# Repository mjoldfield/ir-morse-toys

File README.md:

# Games with Morse Code at 940nm

This repository contains designs for two detectors and two transmitters
for Morse Code signals, all working with 940nm infra-red light.

You can read more on [my website](https://mjoldfield.com/atelier/2022/01/ir-fun.html).

If you’re near Cambridge, UK you might enjoy the [geocache](https://www.geocaching.com/geocache/GC86BQY_to-the-birdhouse)
 for which they were designed.

## Building the firmware

There are three steps:

  1. Install a GNU toolchain. You can download this from
	 [ARM](https://developer.arm.com/Tools%20and%20Software/GNU%20Toolchain),
	 but it is often available as system package in e.g. Debian.

  1. Install [libopencm3](https://libopencm3.org):

		$ git submodule init
		
		$ git submodule upgrade

		$ make -C libopencm3

  1. Compile the firmware

		$ make -C tx-bluepill/firmware

		$ make -C tx-stm32l431/firmware

The libopencm3-rules.mk file contains a number of fake targets to flash the firmware.

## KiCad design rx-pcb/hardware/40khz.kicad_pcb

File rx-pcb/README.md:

# A PCB based Detector

You can read more on [my website](https://mjoldfield.com/atelier/2022/01/rx-pcb.html).

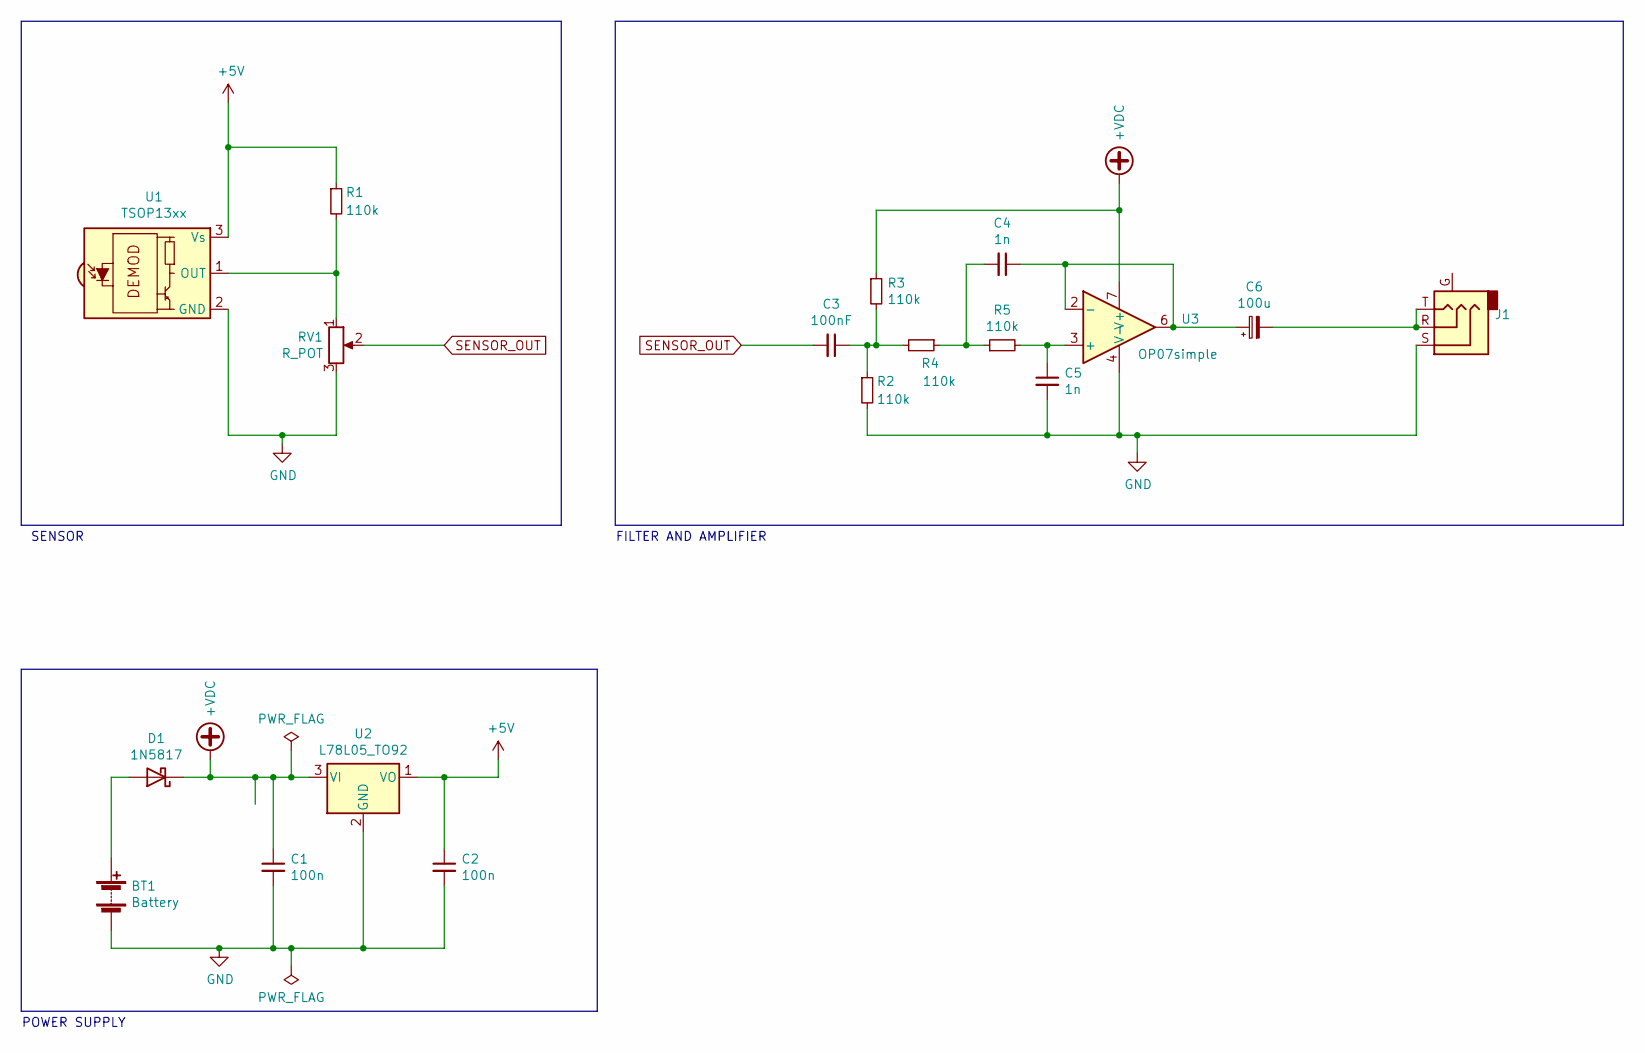
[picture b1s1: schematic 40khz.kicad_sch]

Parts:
BT1: Battery; Battery_Keystone_968
C1, C2: 100n; C_Disc_D10.0mm_W2.5mm_P5.00mm
C3: 100nF; C_Disc_D10.0mm_W2.5mm_P5.00mm
C4, C5: 1n; C_Rect_L10.0mm_W5.0mm_P5.00mm_P7.50mm
C6: 100u; CP_Radial_D6.3mm_P2.50mm
D1: 1N5817; D_DO-41_SOD81_P10.16mm_Horizontal
J1: AudioJack3_Ground; TruConnect_3.5mm_StereoSocket
R1, R2, R3, R4, R5: 110k; R_Axial_DIN0207_L6.3mm_D2.5mm_P10.16mm_Horizontal
RV1: R_POT; Potentiometer_Piher_PC-16_Single_Horizontal
U1: TSOP13xx; Vishay_MINIMOLD-3Pin
U2: L78L05_TO92; TO-92_Inline
U3: OP07simple; DIP-8_W7.62mm_Socket

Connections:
+5V: C2.1, R1.1, U1.3 (Vs), U2.1 (VO)
+VDC: C1.1, D1.1 (K), R3.1, U2.3 (VI), U3.7 (V+)
GND: BT1.2 (-), C1.2, C2.2, C5.2, J1.S, R2.2, RV1.3, U1.2 (GND), U2.2 (GND), U3.4 (V-)
unnamed: BT1.1 (+), D1.2 (A)
unnamed: C3.1, R2.1, R3.2, R4.2
unnamed: C4.1, C6.1, U3.2 (-), U3.6
unnamed: C4.2, R4.1, R5.1
unnamed: C5.1, R5.2, U3.3 (+)
unnamed: C6.2, J1.R, J1.T
unnamed: R1.2, RV1.1, U1.1 (OUT)
SENSOR_OUT: C3.2, RV1.2

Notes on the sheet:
SENSOR
POWER SUPPLY
FILTER AND AMPLIFIER

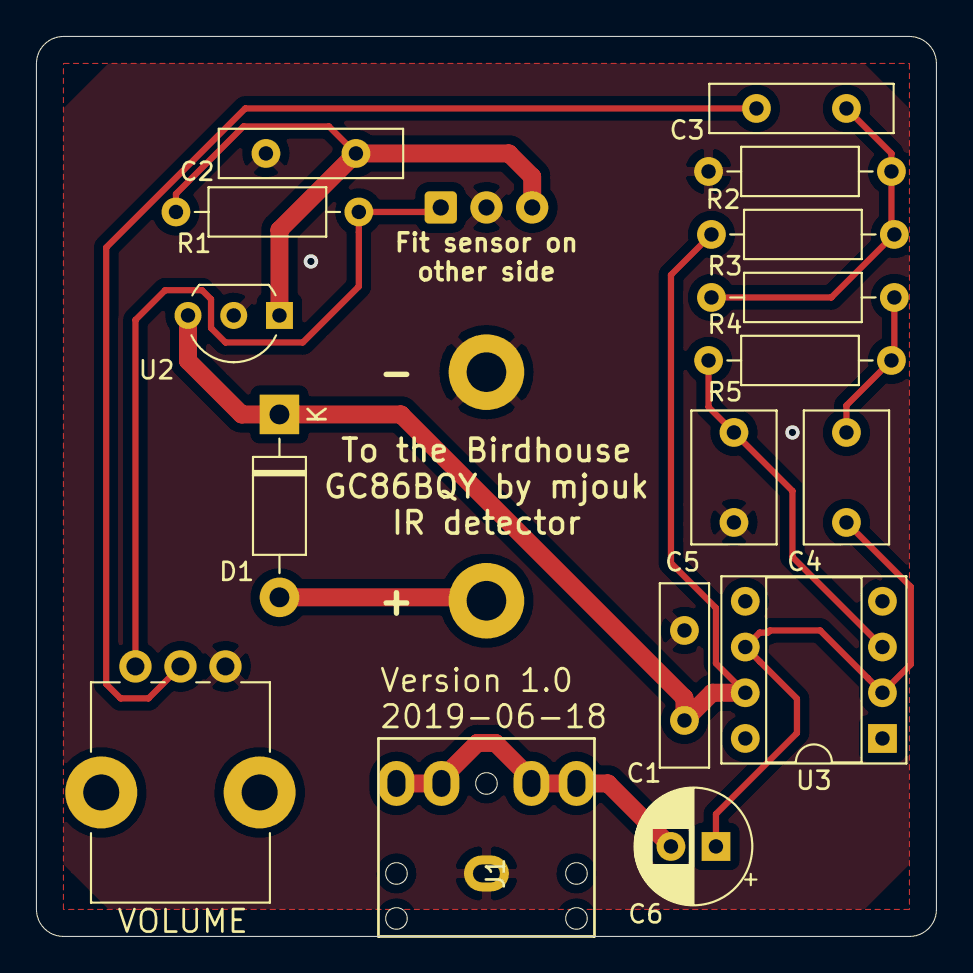
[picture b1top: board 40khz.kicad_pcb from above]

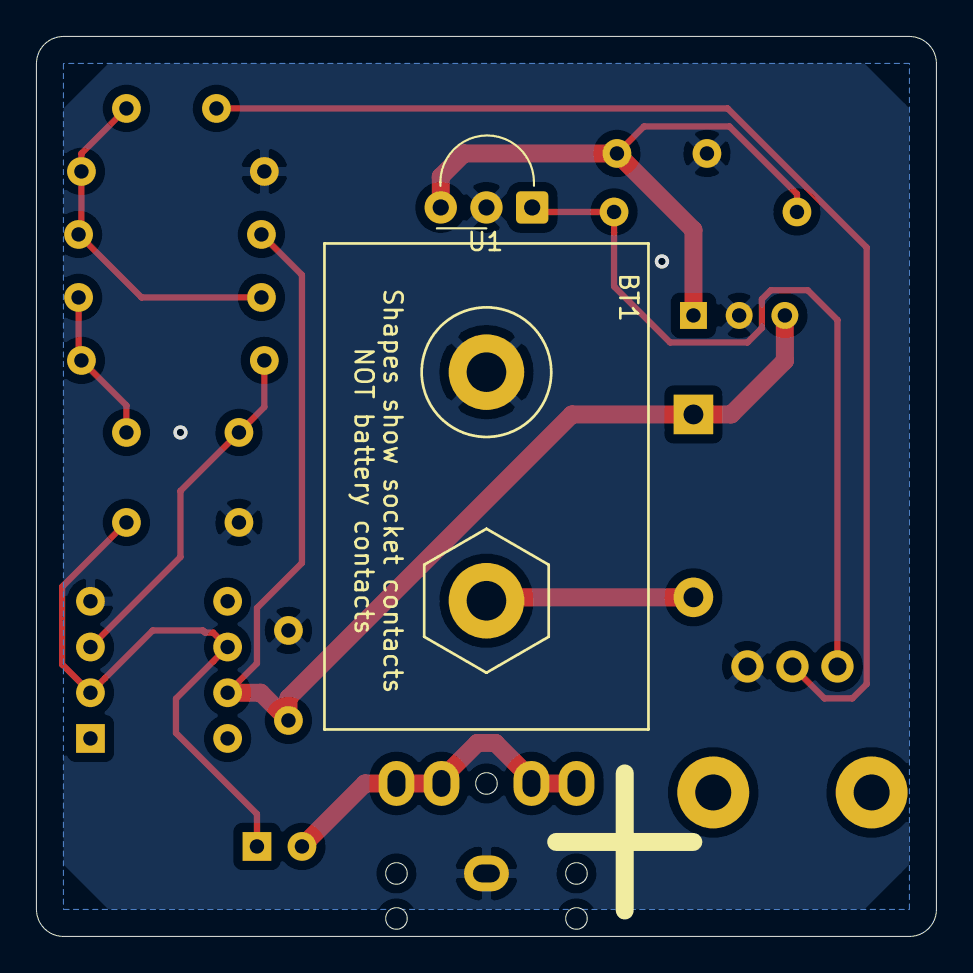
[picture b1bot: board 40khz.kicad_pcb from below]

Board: 2 copper layers, 50.0 x 50.0 mm, 18 parts (2 on the bottom side), 11 nets.

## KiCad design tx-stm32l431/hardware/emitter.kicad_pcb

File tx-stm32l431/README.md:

# A STM32L431 based emitter

You can read more on [my website](https://mjoldfield.com/atelier/2022/01/ir-emitter-bb.html).

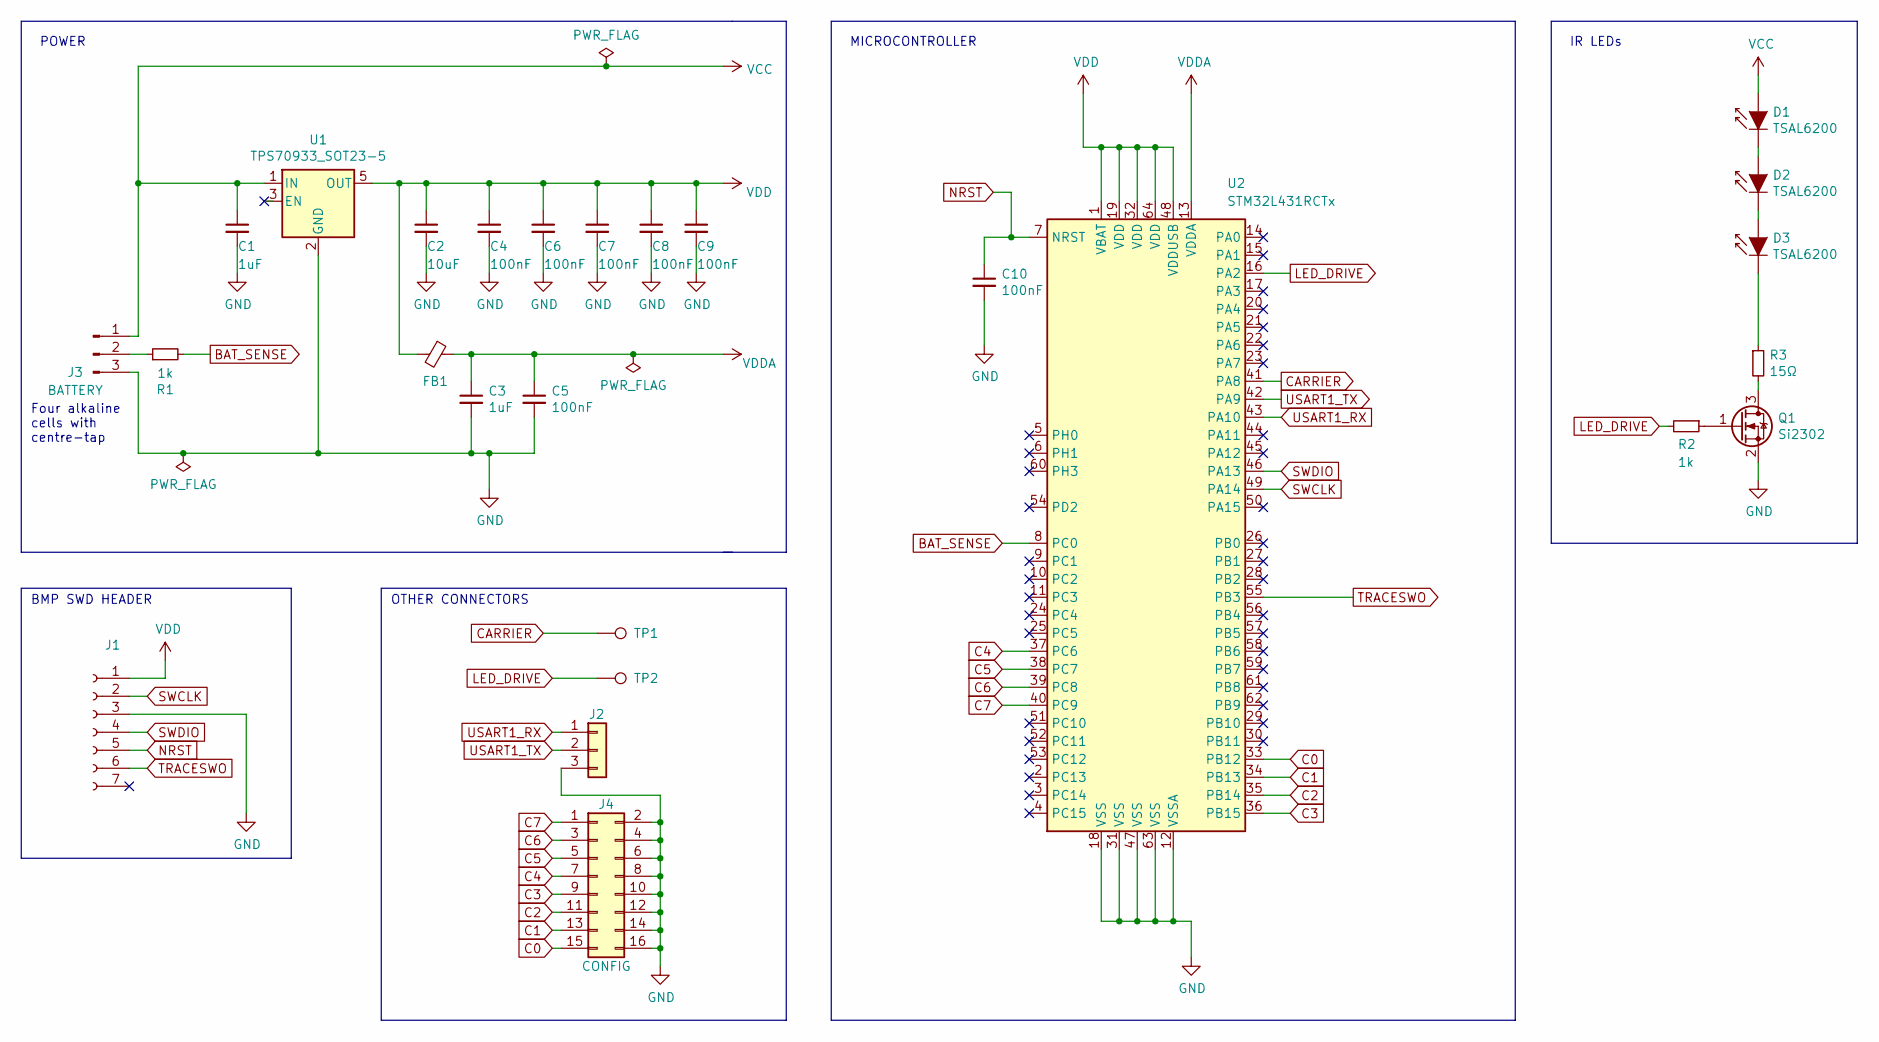
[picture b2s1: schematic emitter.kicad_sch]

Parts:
C1, C3: 1uF; C_0603_1608Metric_Pad1.05x0.95mm_HandSolder
C2: 10uF; C_0603_1608Metric_Pad1.05x0.95mm_HandSolder
C4, C5, C6, C7, C8, C9, C10: 100nF; C_0603_1608Metric_Pad1.05x0.95mm_HandSolder
D1, D2, D3: TSAL6200; LED_D5.0mm_Horizontal_O1.27mm_Z3.0mm_IRBlack
FB1: Ferrite_Bead_Small; L_0603_1608Metric_Pad1.05x0.95mm_HandSolder
J1: Conn_01x07_Female; PinSocket_1x07_P2.54mm_Vertical
J2: Conn_01x03; PinSocket_1x03_P2.54mm_Vertical
J3: BATTERY; PinHeader_1x03_P2.54mm_Vertical
J4: CONFIG; PinHeader_2x08_P2.54mm_Vertical
Q1: Si2302; SOT-23
R1, R2: 1k; R_0603_1608Metric_Pad1.05x0.95mm_HandSolder
R3: 15Ω; R_0603_1608Metric_Pad1.05x0.95mm_HandSolder
TP1, TP2: TestPoint; TestPoint_Loop_D2.60mm_Drill1.4mm_Beaded
U1: TPS70933_SOT23-5; SOT-23-5
U2: STM32L431RCTx; LQFP-64_10x10mm_P0.5mm

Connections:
BAT_SENSE: R1.2, U2.8 (PC0)
C0: J4.15, U2.33 (PB12)
C1: J4.13, U2.34 (PB13)
C2: J4.11, U2.35 (PB14)
C3: J4.9, U2.36 (PB15)
C4: J4.7, U2.37 (PC6)
C5: J4.5, U2.38 (PC7)
C6: J4.3, U2.39 (PC8)
C7: J4.1, U2.40 (PC9)
CARRIER: TP1.1, U2.41 (PA8)
GND: C1.2, C2.2, C3.2, C4.2, C5.2, C6.2, C7.2, C8.2, C9.2, C10.2, J1.3, J2.3, J3.3, J4.2, J4.4, J4.6, J4.8, J4.10, J4.12, J4.14, J4.16, Q1.2 (S), U1.2 (GND), U2.12 (VSSA), U2.18 (VSS), U2.31 (VSS), U2.47 (VSS), U2.63 (VSS)
LED_DRIVE: R2.2, TP2.1, U2.16 (PA2)
NRST: C10.1, J1.5, U2.7 (NRST)
unnamed: D1.1 (K), D2.2 (A)
unnamed: D2.1 (K), D3.2 (A)
unnamed: D3.1 (K), R3.1
unnamed: J3.2, R1.1
unnamed: Q1.1 (G), R2.1
unnamed: Q1.3 (D), R3.2
SWCLK: J1.2, U2.49 (PA14)
SWDIO: J1.4, U2.46 (PA13)
TRACESWO: J1.6, U2.55 (PB3)
USART1_RX: J2.1, U2.43 (PA10)
USART1_TX: J2.2, U2.42 (PA9)
VCC: C1.1, D1.2 (A), J3.1, U1.1 (IN)
VDD: C2.1, C4.1, C6.1, C7.1, C8.1, C9.1, FB1.2, J1.1, U1.5 (OUT), U2.1 (VBAT), U2.19 (VDD), U2.32 (VDD), U2.48 (VDDUSB), U2.64 (VDD)
VDDA: C3.1, C5.1, FB1.1, U2.13 (VDDA)

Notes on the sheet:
BMP SWD HEADER
IR LEDs
MICROCONTROLLER
OTHER CONNECTORS
POWER
Four alkaline cells with centre-tap

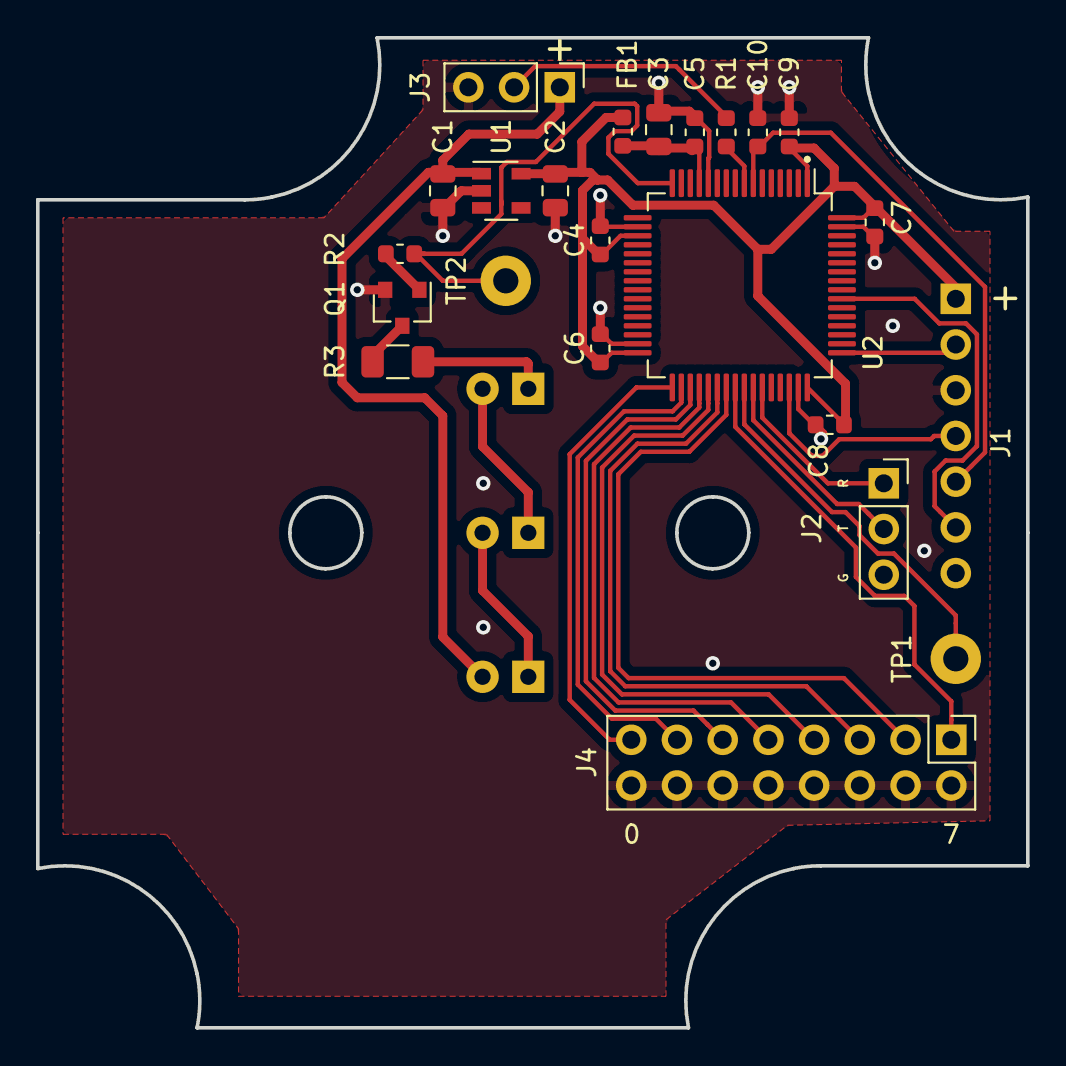
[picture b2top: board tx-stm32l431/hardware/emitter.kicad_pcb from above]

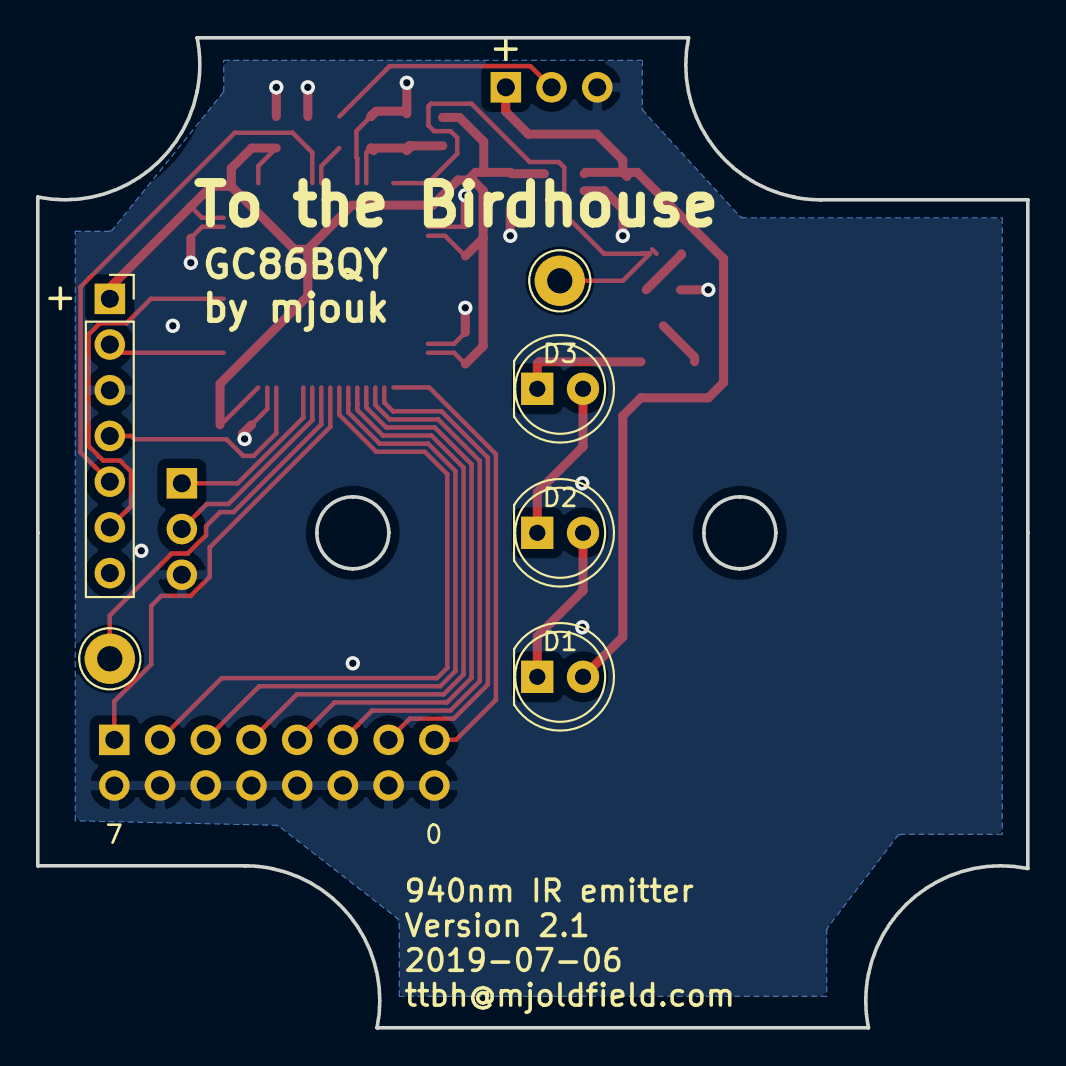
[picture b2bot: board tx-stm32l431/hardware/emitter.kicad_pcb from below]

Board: 2 copper layers, 55.0 x 55.0 mm, 26 parts (6 on the bottom side), 27 nets.

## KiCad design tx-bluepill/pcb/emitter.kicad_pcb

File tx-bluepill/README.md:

# A Bluepill STM32F103 based emitter

You can read more on [my website](https://mjoldfield.com/atelier/2022/01/ir-emitter-bp.html).

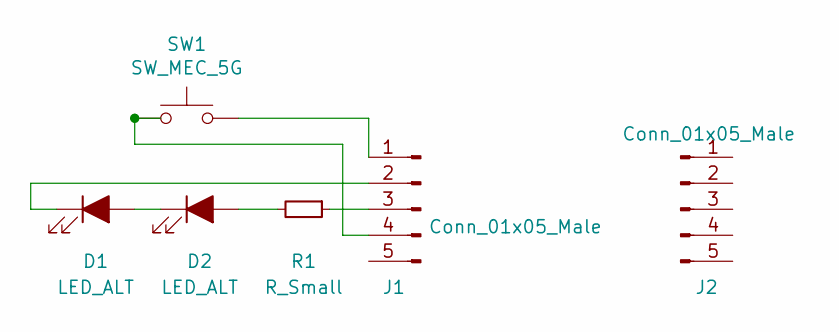
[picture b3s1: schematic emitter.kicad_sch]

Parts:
D1, D2: LED_ALT; LED_D5.0mm
J1, J2: Conn_01x05_Male; PinHeader_1x05_P2.54mm_Vertical
R1: R_Small; R_Axial_DIN0204_L3.6mm_D1.6mm_P5.08mm_Horizontal
SW1: SW_MEC_5G; SW_TH_Tactile_Omron_B3F-10xx

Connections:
unnamed: D1.1 (K), J1.2
unnamed: D1.2 (A), D2.1 (K)
unnamed: D2.2 (A), R1.2
unnamed: J1.1, SW1.3 (B), SW1.4 (B)
unnamed: J1.3, R1.1
unnamed: J1.4, SW1.1 (A), SW1.2 (A)

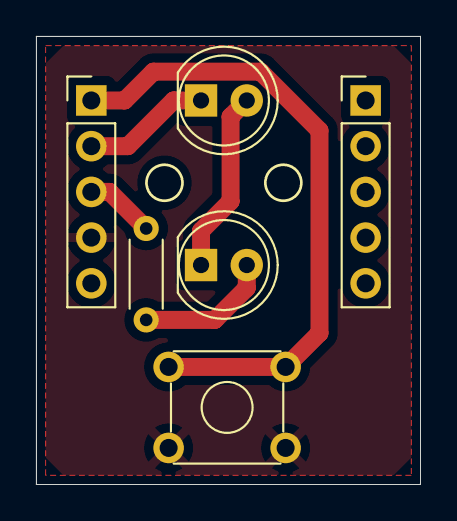
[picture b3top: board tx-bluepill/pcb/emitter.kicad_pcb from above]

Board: 2 copper layers, 21.3 x 24.9 mm, 6 parts (0 on the bottom side), 6 nets.

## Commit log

2022-05-23 A new start
2022-05-23 Fix broken image link
2022-05-23 Fix image size.
2022-05-23 Fix title
2022-05-23 Fix link
2022-05-23 Fix link & image
2022-05-23 Fix link and image
2022-05-23 Fix link and image.
2022-05-24 Added brief instructions to build the firmware
